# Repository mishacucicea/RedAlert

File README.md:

# RedAlert
Extreme Feedback Device for anything!

LightFeeD is a visual feedback device for anything. Capable of producing the whole RGB range of colours and beeping sounds. It is controlled over the internet with a simple API that can be called virtually from anywhere with an Internet connection.  The device is powered with a standard USB charger. The brightness is auto-adjusted depending on your environment so it's not too bright at night, and not too dim during  the day.

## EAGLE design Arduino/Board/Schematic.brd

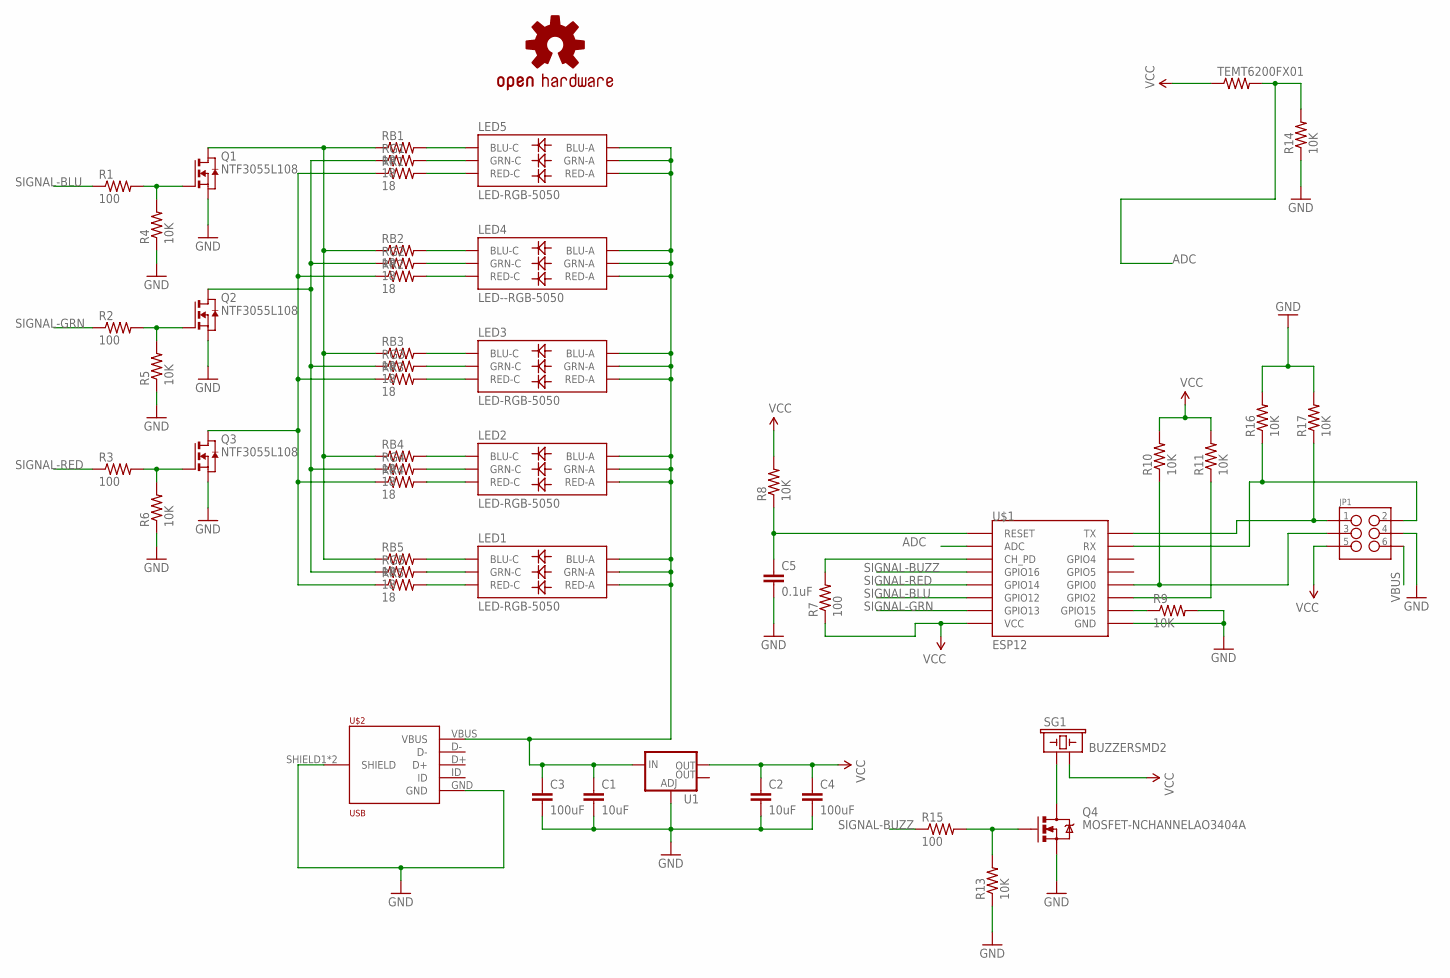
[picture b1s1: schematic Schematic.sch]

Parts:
C1, C2: 10uF; 0603-CAP
C3, C4: 100uF; 1206
C5: 0.1uF; 0603-CAP
JP1: M03X2POGO_PINS; 2X3_POGO
LED1, LED2, LED3, LED5: LED-RGB-5050; LED-TRICOLOR-5050
LED4: LED--RGB-5050; LED-TRICOLOR-5050
LOGO1: OSHW-LOGOM-COPPER; OSHW-LOGO-M_COPPER
Q1, Q2, Q3: NTF3055L108; SOT223HEAT
Q4: MOSFET-NCHANNELAO3404A; SOT23-3
R1, R2, R3, R7, R15: 100; 0805
R4, R5, R6, R8, R9, R10, R11, R13, R14, R16, R17: 10K; 0805
RB1, RB2, RB3, RB4, RB5: 18; 1206
RG1, RG2, RG3, RG4, RG5: 18; 1206
RR1, RR2, RR3, RR4, RR5: 18; 1206
SG1: BUZZERSMD2; BUZZER-CCV
TEMT6200FX01: RESISTOR0805-RES; 0805
U1: V_REG_LM1117SOT223; SOT223
U$1: ESP12
U$2: USB; MICRO-USB3065-30-00-A

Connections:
ADC: R14.2, TEMT6200FX01.2, U$1.ADC
GND: C1.2, C2.2, C3.2, C4.2, C5.2, JP1.P$4 (4), Q1.3 (S), Q2.3 (S), Q3.3 (S), Q4.2 (S), R4.1, R5.1, R6.1, R9.2, R13.1, R14.1, R16.2, R17.2, U1.1 (ADJ), U$1.GND, U$2.GND, U$2.SHIELD1 (SHIELD), U$2.SHIELD2 (SHIELD)
unnamed: LED5.4 (BLU-C), RB1.2
unnamed: LED1.4 (BLU-C), RB5.2
unnamed: LED5.6 (GRN-C), RG1.2
unnamed: Q1.2 (D), Q1.4 (D), Q1.P$1 (D), Q1.P$2 (D), Q1.P$3 (D), Q1.P$4 (D), Q1.P$5 (D), Q1.P$6 (D), Q1.P$7 (D), Q1.P$8 (D), Q1.P$9 (D), Q1.P$10 (D), Q1.P$11 (D), Q1.P$12 (D), Q1.P$13 (D), Q1.P$14 (D), Q1.P$15 (D), Q1.P$16 (D), Q1.P$17 (D), Q1.P$18 (D), Q1.P$19 (D), RB1.1, RB2.1, RB3.1, RB4.1, RB5.1
unnamed: LED5.5 (RED-C), RR1.2
unnamed: Q2.2 (D), Q2.4 (D), Q2.P$1 (D), Q2.P$2 (D), Q2.P$3 (D), Q2.P$4 (D), Q2.P$5 (D), Q2.P$6 (D), Q2.P$7 (D), Q2.P$8 (D), Q2.P$9 (D), Q2.P$10 (D), Q2.P$11 (D), Q2.P$12 (D), Q2.P$13 (D), Q2.P$14 (D), Q2.P$15 (D), Q2.P$16 (D), Q2.P$17 (D), Q2.P$18 (D), Q2.P$19 (D), RG1.1, RG2.1, RG3.1, RG4.1, RG5.1
unnamed: LED4.4 (BLU-C), RB2.2
unnamed: Q3.2 (D), Q3.4 (D), Q3.P$1 (D), Q3.P$2 (D), Q3.P$3 (D), Q3.P$4 (D), Q3.P$5 (D), Q3.P$6 (D), Q3.P$7 (D), Q3.P$8 (D), Q3.P$9 (D), Q3.P$10 (D), Q3.P$11 (D), Q3.P$12 (D), Q3.P$13 (D), Q3.P$14 (D), Q3.P$15 (D), Q3.P$16 (D), Q3.P$17 (D), Q3.P$18 (D), Q3.P$19 (D), RR1.1, RR2.1, RR3.1, RR4.1, RR5.1
unnamed: LED4.6 (GRN-C), RG2.2
unnamed: LED4.5 (RED-C), RR2.2
unnamed: LED3.4 (BLU-C), RB3.2
unnamed: LED3.6 (GRN-C), RG3.2
unnamed: LED3.5 (RED-C), RR3.2
unnamed: LED2.4 (BLU-C), RB4.2
unnamed: LED2.6 (GRN-C), RG4.2
unnamed: LED2.5 (RED-C), RR4.2
unnamed: LED1.6 (GRN-C), RG5.2
unnamed: LED1.5 (RED-C), RR5.2
unnamed: Q1.1 (G), R1.2, R4.2
unnamed: Q2.1 (G), R2.2, R5.2
unnamed: Q3.1 (G), R3.2, R6.2
unnamed: R7.2, U$1.CH_PD
unnamed: JP1.P$3 (3), R10.1, U$1.GPIO0
unnamed: C5.1, R8.1, U$1.RESET
unnamed: R11.1, U$1.GPIO2
unnamed: R9.1, U$1.GPIO15
unnamed: JP1.P$1 (1), R17.1, U$1.TX
unnamed: JP1.P$2 (2), R16.1, U$1.RX
unnamed: Q4.1 (G), R13.2, R15.2
unnamed: Q4.3 (D), SG1.+ (1)
SIGNAL-BLU: R1.1, U$1.GPIO12
SIGNAL-BUZZ: R15.1, U$1.GPIO16
SIGNAL-GRN: R2.1, U$1.GPIO13
SIGNAL-RED: R3.1, U$1.GPIO14
VBUS: C1.1, C3.1, JP1.P$6 (6), LED1.1 (GRN-A), LED1.2 (RED-A), LED1.3 (BLU-A), LED2.1 (GRN-A), LED2.2 (RED-A), LED2.3 (BLU-A), LED3.1 (GRN-A), LED3.2 (RED-A), LED3.3 (BLU-A), LED4.1 (GRN-A), LED4.2 (RED-A), LED4.3 (BLU-A), LED5.1 (GRN-A), LED5.2 (RED-A), LED5.3 (BLU-A), U1.3 (IN), U$2.VBUS
VCC: C2.1, C4.1, JP1.P$5 (5), R7.1, R8.2, R10.2, R11.2, SG1.- (2), TEMT6200FX01.1, U1.2 (OUT), U$1.VCC

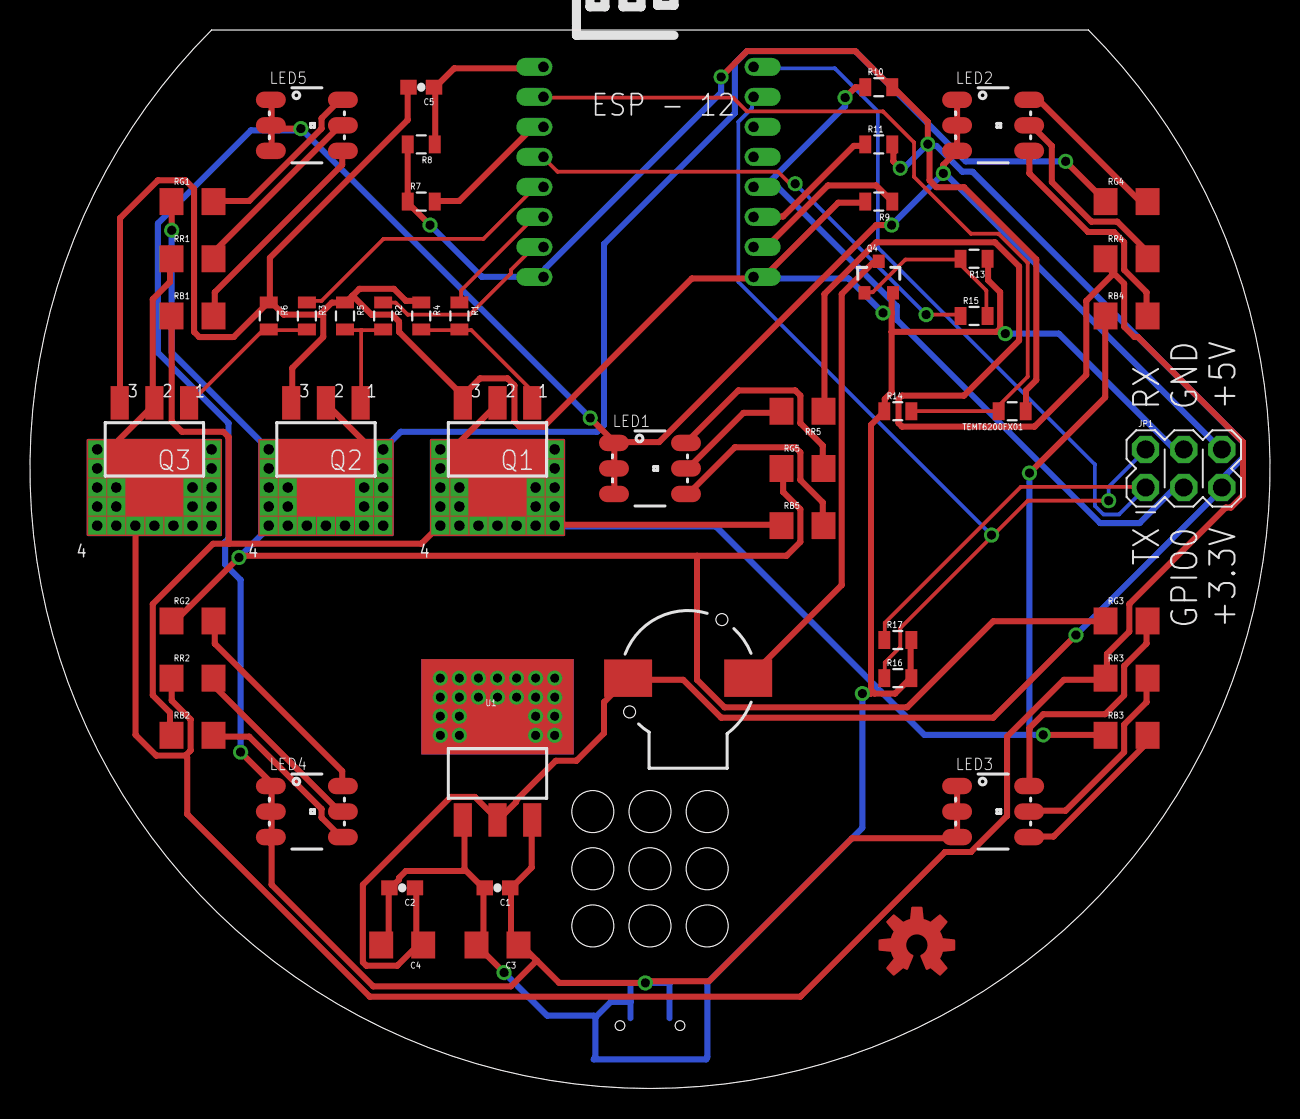
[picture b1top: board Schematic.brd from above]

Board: 2 copper layers, 82.6 x 70.5 mm, 52 parts (1 on the bottom side), 38 nets.

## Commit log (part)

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2016-06-03 added favicon
2016-06-03 added receipe
2016-06-05 Ignoring Web.Debug.config instead of Web.config
2016-06-05 Added EF reference and renamed models.
2016-06-06 working on the firmware
2016-06-06 added designs
2016-06-06 added images
2016-06-06 binding the DeviceIdentity controller to the database.
2016-06-07 changing the functionality for device registration and device getting connection info
2016-06-08 fixed the error on device registration page
2016-06-08 updated layout with drop down menu
2016-06-08 Added Id for models.
2016-06-08 debugging the device registration process
2016-06-09 added new images and and scroller
2016-06-09 fixed color css issue
2016-06-09 deleted unused files
2016-06-09 added new files
2016-06-10 added file for runtime configuration
2016-06-10 ignoring files
2016-06-10 addded new template for views
2016-06-10 updated the configuration setup
2016-06-10 added color picker and generate url
2016-06-10 Added mood mode
2016-06-10 changed size for page added logo redirect
2016-06-10 various work..
2016-06-11 small fixes
2016-06-11 fixed api URL
2016-06-11 receipes to recipes
2016-06-11 updated the config.
2016-06-11 change template for some views and fixed css for menu
2016-06-11 Adding NLog, BaseController and Application_Error in global.asax.
2016-06-11 Remove extra key from web.config.
2016-06-11 Adding exception handler for web api.
2016-06-11 added group management
2016-06-11 Added log.txt to ignore list.
2016-06-11 working on fixing SAS token generation
2016-06-11 working on fixing sas toke ngeneration
2016-06-11 working on the SAS generatoin
2016-06-11 fixed authentication api requests
2016-06-21 added send to group
2016-06-22 added localstorage and qrcode based on saved color
2016-06-22 save credentials in localstorage
2016-06-22 some verification for colors
2016-06-22 added mood and qrcode to send message
2016-06-22 rename controller
2016-06-23 added textboxes instead of localstorage
2016-06-23 adding patterns support
2016-06-24 Added Voting
2016-06-24 change url
2016-06-24 changed QrCode
2016-06-24 fixing patterns. refactoring
2016-06-24 merge!
2016-06-24 refactorings and improvements in the voting.
2016-06-24 added firmware for testing
2016-06-24 added update functionality.
2016-06-25 Redirect to Error view in case of error. Separated header and footer into individual views.
2016-06-25 Unified the layout to remove duplicate markup.
2016-06-25 updated the firmware for automatic update
2016-06-25 Add error if the serial number is invalid.
2016-06-25 Fixed web.release.config.
2016-06-25 fixing message sending issues.
2016-06-25 fixed the firmware for OTA
2016-06-25 fixed the firmware for OTA (yet again..)
2016-06-25 Remove unnecessary references to redalertxfd.azurewebsites.net.
2016-06-25 adding debug code to debug the OTA problems
2016-06-25 fixed OTA
2016-06-25 trying to fix the MD5 issue for the OTA
2016-06-25 fixing html... how did I end up doing that?
2016-06-25 updated firmware
2016-06-25 forgot to include the firmware file into the project
2016-06-25 removed useless debug line
2016-06-25 updated firmware to correctly handle the WAVES pattern.
2016-06-25 fixed the pattern on the API side.
2016-06-26 Added DeviceList method and other minor fixes. Removed DeviceIdentityController as it was no longer used.
2016-06-26 Narrow navigation menu. Adding device list and device details views and actions.
2016-06-27 Created a new view to try a simplified color picker.
2016-06-28 Fix sending the color in the Mood.cshtml and sizing of the colorpicker.
2016-06-28 Adjusting picker position.
2016-06-28 Trying yet another css fix.
2016-06-28 Trying a separate mood page for a mobile issue.
2016-06-28 Adjusting css to see if that's the issue.
2016-06-28 .color width changed to 0.
2016-06-28 Attempt #3.
2016-06-28 Finally - colorpicker fixed on mobile. 0 width had to do with it.
2016-06-28 Remove the old "Mood" page and replace the menu item with the new one.
2016-06-29 Added device name and parameter entry for mood page.
2016-06-29 Added extra bits of loging for device authentication
2016-06-29 Have a read only textbox for the url details as it was looking ugly on mobile.
2016-06-29 Make logging roll files greater than 1MB.
2016-06-29 added new description for home page
2016-06-29 fixed sneaky bug on device authentication after the first message was sent to device.
2016-06-30 Removed some try/catch blocks. Removed lorem ipsum text. Fix for group sending.
2016-06-30 added reset button
2016-06-30 changed url for voting
2016-06-30 added new styles for voting
2016-06-30 Setting device key on details.
2016-06-30 Adding quotes to sender key.
2016-06-30 added new stuff
2016-06-30 fixed senderKey
2016-06-30 fixed pattern and send url
2016-06-30 Adding Demo controller and view.
2016-06-30 fixed new thing
2016-06-30 Add voting link to the demo view.
2016-06-30 Changed device ID for demo.
2016-06-30 Adjusted device id for mood.
2016-07-01 Adding Application Insights.
2016-07-01 added application insights telemetry
2016-07-01 run away train .. adding second part of the commit
2016-07-01 fixed application insights
2016-07-01 updating packages. removing help pages.
2016-07-04 added new layout
2016-07-04 deleted css, fixed layout, added grid
2016-07-04 Added Authentication
2016-07-04 deleted SqlCompact
2016-07-04 deleted dll
2016-07-05 added google login
2016-07-06 deleted unused css
2016-07-07 added layout for list of devices
2016-07-07 changed layout for url and adding color field
2016-07-07 added layout for qrCode
2016-07-08 added layout for voting
2016-07-08 added layout for authentication
2016-07-08 changed layout for some account partials
2016-07-08 pcb upgrade
    changed:
    - bigger (size) resistors for LEDs
    - changed MOSFETs for more power
    - added ambient light sensors
2016-07-08 added buzzer
    added buzzer and holes for air flow
2016-07-09 updated firmware with newer Arduino Core version
2016-07-09 fixing firmware update..
2016-07-11 corrected the bundling and missing file errors.
2016-07-11 corrected the corrected the bundling and missing file errors.
2016-07-11 updated the board design
    updated to the requirements in the https://trello.com/c/WxGEJiPR
2016-07-12 small fixes to the board.
2016-07-18 small improvements in the firmware
2016-07-19 performance improve& login providers& deleted forms auth
2016-07-31 migrating project to Platform IO
2016-07-31 refactoring arduino code
2016-07-31 trying to make real-time verification of the user input
2016-07-31 updated the configuration setting message.
2016-08-01 cleanup
2016-08-01 Layout changes on Register device view.
2016-08-01 Prevent double registration with same serial number - no matter the account.
2016-08-01 added colour cycling in case of problems.
2016-08-01 added per device SSID generation
2016-08-02 Reset sender/device keys.
2016-08-02 Remove device (from the MyDevices page).
2016-08-02 getting the async data verification to work..
2016-08-02 enhanced the UX when configuring the device
2016-08-02 Merge branch 'arduino-UX'
    # Conflicts:
    # Arduino/RedAlert/RedAlert/WiFiSetup.cpp
2016-08-02 correcting the brand
2016-08-03 some small changes
2016-08-04 Fixed Owin dlls version and added mime type for webp.
2016-08-04 Temporary added AllowAnonymous on BaseController. Hub device Id is now hidden from device details.
2016-08-05 styling fixes
2016-08-06 design fixes
2016-08-08 - added Online/Offline indicator for the device list. - adjusted designto be centered.
2016-08-09 made some changes on login and layout
2016-08-10 implementing support for a secondary IoT Hub for redundancy
2016-08-11 Add trace debug to see why NLog is not working.
2016-08-11 small issue.
2016-08-12 updated nuget packages
2016-08-16 some minor changes
2016-08-16 fixed login cached bug
2016-08-16 added woff2
2016-08-18 added redirect from www to non-www
2016-08-18 fixed layout and some issues
2016-08-18 fixed details page
2016-08-18 added bindings from view to controller
2016-08-19 added live id &fixed layout
2016-08-23 fixed layout, eliminated some hardcordings, refactoring
2016-08-25 excluded debugconfig
2016-09-03 added support for secondary IoT Hub for the firmware
2016-09-03 updated OTA Update functionality
2016-09-04 added feature toggles to the firmware
2016-09-06 some changes on home page
2016-09-08 add register method
2016-09-14 fexed startup id hardcodeings
2016-09-14 excluded debug
2016-09-14 commented login email claim
2016-09-16 add email field on register & added new page for adding new device to user
2016-09-16 Revert "add email field on register & added new page for adding new device to user"
    This reverts commit 49b9a230bd3d51e079dd35f5bdd26ddc3e518950.
2016-09-16 delete
2016-11-06 updated board (Rev. 3)
2016-11-07 debugconfig.json should not be in the csproj file.
2017-01-23 moving to V3. set the ambient light check into a region that will be unnoticeable to the user.
2017-01-24 improvements

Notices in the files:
parts and their libraries:
SparkFun-Capacitors: Licensing: Creative Commons ShareAlike 4.0 International - https://creativecommons.org/licenses/by-sa/4.0
